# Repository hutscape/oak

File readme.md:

# Oak

> 🌳 Outdoor LoRa-GPS tracker with E-Ink display  🔑

Visit [hutscape.com/oak](https://hutscape.com/oak) for more details.

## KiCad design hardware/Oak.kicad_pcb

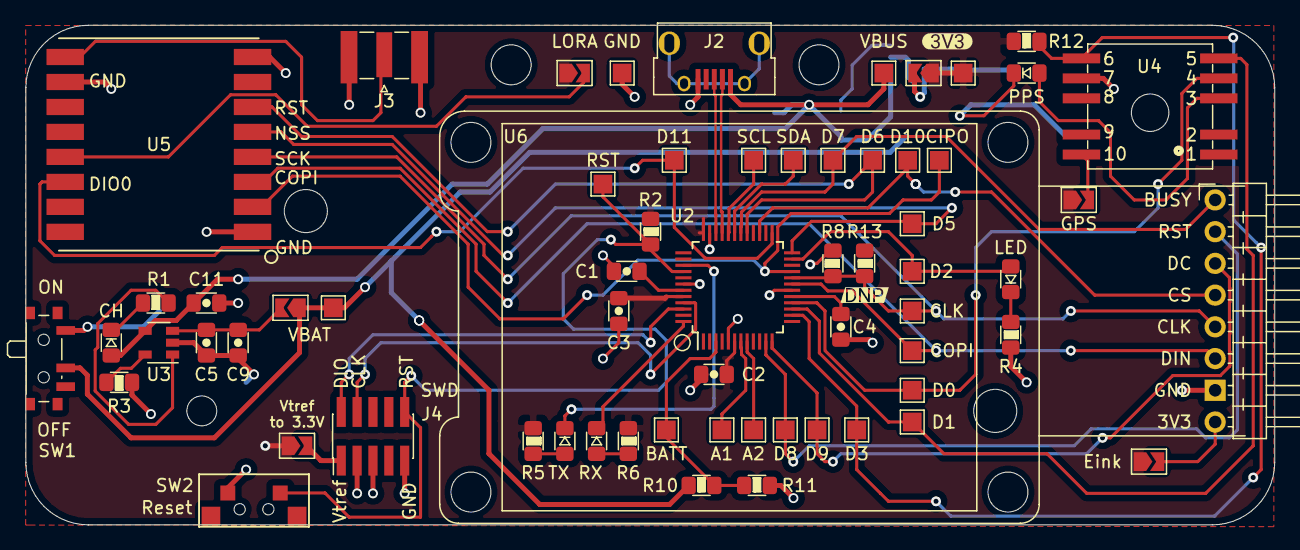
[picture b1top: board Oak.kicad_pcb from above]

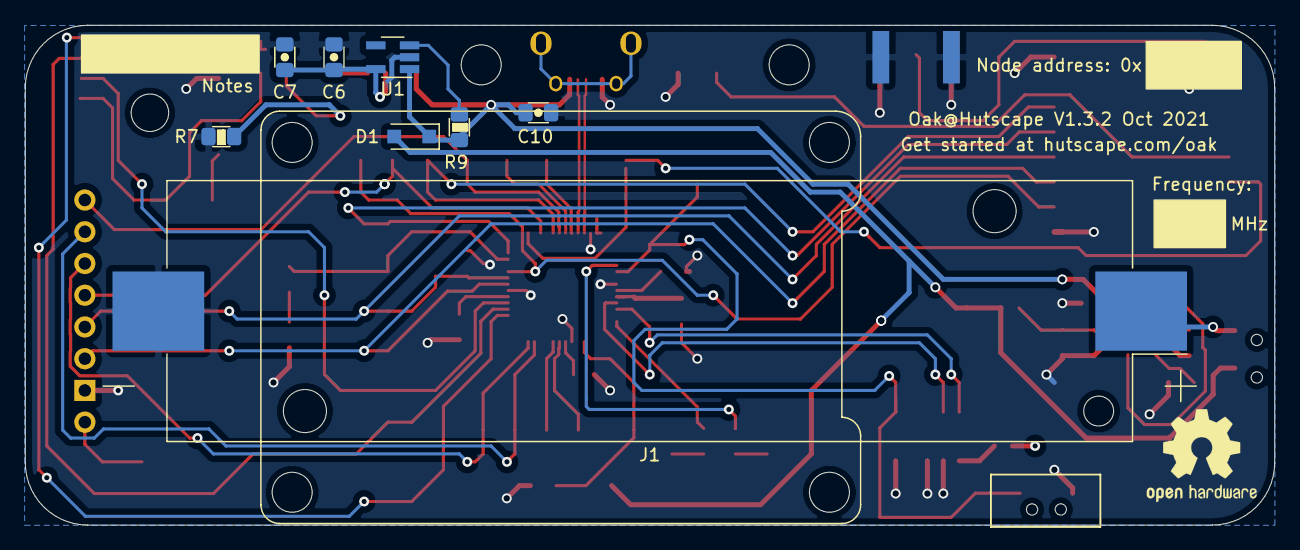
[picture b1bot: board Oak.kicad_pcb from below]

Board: 2 copper layers, 100.0 x 40.0 mm, 73 parts (8 on the bottom side), 48 nets.

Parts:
C1, C7, C9: 1uF; C_0805_2012Metric_Pad1.15x1.40mm_HandSolder
C2, C3, C4: 100nF; C_0805_2012Metric_Pad1.15x1.40mm_HandSolder
C5, C6, C10, C11: 10uF; C_0805_2012Metric_Pad1.15x1.40mm_HandSolder
D1: D_Schottky; D_SOD-123F
D2: ORANGE; LED_0805_2012Metric_Pad1.15x1.40mm_HandSolder
D3: RED; LED_0805_2012Metric_Pad1.15x1.40mm_HandSolder
D4, D5, D6: YELLOW; LED_0805_2012Metric_Pad1.15x1.40mm_HandSolder
J1: 18650 Battery holder; BatteryHolder_Keystone_1042_1x18650
J2: USB_B_Micro; USB_Micro-B_Horizontal-U254-051T-4BH23-S2B
J3: Conn_Coaxial; SMA_Samtec_SMA-J-P-X-ST-EM1_EdgeMount
J4: Conn_ARM_JTAG_SWD_10; PinHeader_2x05_P1.27mm_Vertical_SMD
JP1, JP2, JP3, JP4, JP5, JP6: SolderJumper_2_Open; SolderJumper-2_P1.3mm_Open_TrianglePad1.0x1.5mm
R1, R4, R5, R6, R7, R8: 1k; R_0805_2012Metric_Pad1.15x1.40mm_HandSolder
R2, R3, R12: 10k; R_0805_2012Metric_Pad1.15x1.40mm_HandSolder
R9, R10, R11: 100k; R_0805_2012Metric_Pad1.15x1.40mm_HandSolder
R13: DNP; R_0805_2012Metric_Pad1.15x1.40mm_HandSolder
SW1: SW_SPDT; SW_SPDT_PCM12
SW2: SW_Push; Tactile_pushbutton
TP1, TP2, TP3, TP4, TP5, TP6, TP7, TP8, TP9, TP10, TP11, TP12, TP13, TP14, TP15, TP16, TP17, TP18, TP19, TP20, TP21, TP22, TP23, TP24: TestPoint_Probe; TestPoint_Pad_1.5x1.5mm
U1: AP2112; SOT-23-5_HandSoldering
U2: ATSAMD21; TQFP-48_7x7mm_P0.5mm
U3: MCP7383; SOT-23-5
U4: PA1010D; CDTop_MT3333_PA1010D
U5: RFM95; HopeRF_RFM9X-SMD
U6: Waveshare_1in54_epaper; Waveshare_1.54_E-Ink
e: G***; label
svg2mod: G***; label

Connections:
+3V3: C2.1, C3.1, C4.1, JP1.1, JP3.1, JP4.1, JP5.1, JP6.1, R2.1, R5.1, R6.1, R12.1, R13.1, TP4.1, U2.6, U2.17, U2.36, U2.44
/A1: TP7.1, U2.7
/A2: TP6.1, U2.8
/BATT: R10.2, R11.1, TP8.1, U2.3
/CIPO: TP21.1, U2.21, U5.2
/CLK: R8.1, R13.2, TP16.1, U2.20, U5.4, U6.5
/COPI: TP5.1, U2.19, U5.3, U6.6
/EINK_BUSY: TP19.1, U2.30, U6.1
/EINK_CS: TP22.1, U2.27, U6.4
/EINK_DC: TP10.1, U2.12, U6.3
/EINK_RST: TP9.1, U2.11, U6.2
/GPS_RST: R12.2, TP11.1, U2.14, U4.6
/GPS_RX: TP12.1, U2.15, U4.5
/GPS_TX: TP13.1, U2.16, U4.4
/LED: D6.2, TP14.1, U2.23
/LORA_CS: TP15.1, U2.24, U5.5
/LORA_DATA: TP24.1, U2.25, U5.14
/LORA_RST: TP20.1, U2.29, U5.6
/RST: J4.10, R2.2, SW2.1, TP23.1, U2.40
/RX_LED: D5.1, U2.48
/SCL: TP18.1, U2.32
/SDA: TP17.1, U2.31
/SWCLK: J4.4, U2.45
/SWDIO: J4.2, U2.46
/TX_LED: D4.1, U2.39
/USB_D+: J2.3, U2.34
/USB_D-: J2.2, U2.33
/VBAT: D1.2, JP2.1, R10.1, SW1.2, TP1.1
/VBUS: C10.1, C11.2, D1.1, D2.2, J2.1, R9.2, TP2.1, U1.1, U3.4
GND: C1.1, C2.2, C3.2, C4.2, C5.1, C6.2, C7.2, C9.1, C10.2, C11.1, J1.2, J2.5, J3.2, J4.3, J4.5, J4.9, R3.1, R4.2, R7.2, R8.2, R11.2, SW2.2, TP3.1, U1.2, U2.5, U2.18, U2.35, U2.42, U3.2, U4.7, U5.1, U5.8, U5.10, U6.7
unnamed: C1.2, U2.43
unnamed: C5.2, C9.2, JP2.2, U3.3
unnamed: C6.1, C7.1, JP1.2, U1.5
unnamed: D2.1, R1.1
unnamed: D3.1, R7.1
unnamed: D3.2, U4.3
unnamed: D4.2, R5.2
unnamed: D5.2, R6.2
unnamed: D6.1, R4.1
unnamed: J1.1, SW1.1
unnamed: J3.1, U5.9
unnamed: J4.1, JP6.2
unnamed: JP3.2, U4.10
unnamed: JP4.2, U5.13
unnamed: JP5.2, U6.8
unnamed: R1.2, U3.1
unnamed: R3.2, U3.5
unnamed: R9.1, U1.3

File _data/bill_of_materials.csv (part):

"Designator","Value","Qty","Package","Category","Stock","Manufacturer","MPN","Datasheet","Vendor","Link","Unit","Total","MOQ","Description","DNP"
"C4, C3, C2, ","100nF","3","0805","Electronics","boxA-53","Murata","GCM21BR72A104KA37L","http://www.farnell.com/datasheets/2048170.pdf","Element14","https://sg.element14.com/murata/gcm21br72a104ka37l/cap-0-1-f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","0.207","0.62","5","C_Small: Unpolarized capacitor, small symbol",""
"C5, C6, C10, C11, ","10uF","4","0805","Electronics","boxA-30","Taiyo Yuden","LMK212ABJ106KGHT","http://www.farnell.com/datasheets/2842314.pdf","Element14","https://sg.element14.com/taiyo-yuden/lmk212abj106kght/capaci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","0.252","1.01","1","C_Small: Unpolarized capacitor, small symbol",""
"C7, C9, C1, ","1uF","3","0805","Electronics","boxB-186","Kemet","C0805C105K3RACTU","https://api.kemet.com/component-edge/download/specsheet/C080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","Element14","https://sg.element14.com/kemet/c0805c105k3ractu/cap-1-f-25v-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","0.156 ","0.47","10","C_Small: Unpolarized capacitor, small symbol",""
"D1, ","D_Schottky","1","SOD-123F","Electronics","boxA-52","Nexperia","PMEG3020EH,115","http://www.farnell.com/datasheets/676305.pdf","Element14","https://sg.element14.com/nexperia/pmeg3020eh-115/diode-schot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,115","0.438 ","0.44","5","D_Schottky: Schottky diode",""
"D2, ","ORANGE LED","1","0805","Electronics","","ROHM","SML-211DTT86","http://www.farnell.com/datasheets/2292362.pdf","Element14","https://sg.element14.com/rohm/sml-h12d8tt86/led-orange-63mcd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","0.562","0.562","1","LED: Light emitting diode",""
"D3, ","RED LED","1","0805","Electronics","boxB-187","KINGBRIGHT","KP-2012SURCK","http://www.farnell.com/datasheets/2046343.pdf","Element14","https://sg.element14.com/kingbright/kp-2012surck/led-1-25mm-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","0.474","4.74","5","LED: Light emitting diode",""
"D4, D5, ","YELLOW LED","2","0805","Electronics","boxA-54","Everlight","17-215UYC/S530-A3/TR8","https://datasheet.lcsc.com/szlcsc/1810051702_Everlight-Elec-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","LCSC","https://lcsc.com/product-detail/Light-Emitting-Diodes-LED_08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","0.0624","0.12","10","LED: Light emitting diode",""
"J1, ","18650 polarised Battery holder for button-top batteries","1","SMD","Connector","boxD-power-013","Keystone","1042P","http://www.farnell.com/datasheets/2067690.pdf","Element14","https://sg.element14.com/keystone/1042p/battery-holder-18650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","4.04","4.04","1","Conn_01x02_Female: Generic connector, single row, 01x02, script generated (kicad-library-utils/schlib/autogen/connector/)",""
"J2, ","USB_B_Micro","1","SMD","Connector","boxA-60 ","XKB Connectivity","U254-051T-4BH23-S2B","https://datasheet.lcsc.com/szlcsc/2002271812_XKB-Connectivit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","LCSC","https://lcsc.com/product-detail/USB-Connectors_XKB-Connectiv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","0.0786","0.08","10","USB_B_Micro: USB Micro Type B connector",""
"J3, ","Conn_Coaxial","1","PCB Mount","Connector","boxB-185","Multicomp","MP-19-70-4-TGG","http://www.farnell.com/datasheets/1662283.pdf","Element14","https://sg.element14.com/multicomp/19-70-4-tgg/rf-coaxial-sm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","5.16","5.16","1","Conn_Coaxial: coaxial connector (BNC, SMA, SMB, SMC, Cinch/RCA, ...)",""
"J4, ","Conn_ARM_JTAG_SWD_10","1","SMD","Connector","boxC-boards-017","AliExpress Stlxy ","2x5PIN 1.27mm connector","https://www.aliexpress.com/item/4000979986011.html","AliExpress","https://www.aliexpress.com/item/4000979986011.html","0.126","0.126","10","10PCS SMD SMT 2*5 PIN double row male PIN HEADER 1.27MM PITCH Strip Connector",""
"JP1, JP2, JP3, JP4, JP5, ","SolderJumper_2_Open","5","","Connector","","","","","","","","0","","SolderJumper_2_Open: Solder Jumper, 2-pole, open","JP1, JP2, JP3, JP4, JP5"
"R3, R12, R2, ","10k","3","0805","Electronics","boxA-31","Multicomp","MCWF08P1002FTL","http://www.farnell.com/datasheets/2864032.pdf","Element14","https://sg.element14.com/multicomp/mcwf08p1002ftl/res-10k-1-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","0.01","0.03","10","R_Small: Resistor, small symbol",""
"R5, R6, R8, R7, R1, ","1k","5","0805","Electronics","boxA-18","Multicomp","MCWR08X1001FTL","http://www.farnell.com/datasheets/2563624.pdf","Element14","https://sg.element14.com/multicomp/mcwr08x1001ftl/res-1k-1-0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","0.012","0.06","10","R_Small: Resistor, small symbol",""
"R9, R10, R11, ","100k","3","0805","Electronics","boxA-56","Ralec","RTT051003BTP","https://datasheet.lcsc.com/szlcsc/1810301245_RALEC-RTT051003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","LCSC","https://lcsc.com/product-detail/Chip-Resistor-Surface-Mount_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","0.0472","0.14","20","R_Small: Resistor, small symbol",""
"R13, ","DNP","1","0805","Electronics","boxA-18","Multicomp","MCWR08X1001FTL","http://www.farnell.com/datasheets/2563624.pdf","Element14","https://sg.element14.com/multicomp/mcwr08x1001ftl/res-1k-1-0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","0.012","0.06","10","R_Small: Resistor, small symbol","R13"
"SW1, ","SW_SPDT","1","SMD","Switch","boxA-40","Nidec","CUS-12TB","http://www.farnell.com/datasheets/2604293.pdf","Element14","https://sg.element14.com/nidec-copal/cus-12tb/slide-switch-s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","1.04 ","1.04","5","SW_SPDT: Switch, single pole double throw",""
"SW2, ","SW_Push","1","SMD","Switch","boxA-14","RTLECS","RTLECS Tactile side-actuated switch","https://www.aliexpress.com/item/32645332799.html","AliExpress","https://www.aliexpress.com/item/32645332799.html","0.19","0.19","10","SW_Push: Push button switch, generic, two pins",""
"TP13, TP9, TP12, TP14, TP11, TP15, TP20, TP19, TP22, TP23, TP5, TP21, TP16, TP1, TP2, TP10, TP17, TP18, TP8, TP6, TP7, TP4, TP3, TP24, ","TestPoint_Probe","24","SMD","Electronics","","","","","","","","0","","TestPoint_Probe: test point (alternative probe-style design)","TP13, TP9, TP12, TP14, TP11, TP15, TP20, TP19, TP22, TP23, TP5, TP21, TP16, TP1, TP2, TP10, TP17, TP18, TP8, TP6, TP7, TP4, TP3, TP24, "
"U1, ","AP2112","1","SOT23-5","Electronics","boxA-6","Diodes","AP2112K-3.3TRG1","https://www.diodes.com/assets/Datasheets/AP2112.pdf","Element14","https://sg.element14.com/diodes-inc/ap2112k-3-3trg1/ldo-fixe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","0.483","0.48","5","AP2112K-3.3: 600mA low dropout linear regulator, with enable pin, 3.8V-6V input voltage range, 3.3V fixed positive output, SOT-23-5",""
"U2, ","ATSAMD21","1","TQFP-48","Electronics","boxA-59 ","Atmel","ATSAMD21G18A-AU","http://ww1.microchip.com/downloads/en/DeviceDoc/SAM_D21_DA1_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","Element14","https://sg.element14.com/microchip/atsamd21g18a-au/mcu-32bit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","5.46","5.46","1","ATSAMD21G18A-AUT: SAM D21 Microchip SMART ARM-based Flash MCU, 48Mhz, 256K Flash, 32K SRAM, TQFP-48",""
"U3, ","MCP7383","1","SOT-23-5","Electronics","boxB-158","Microchip","MCP73831T-2ACI/OT","http://ww1.microchip.com/downloads/en/DeviceDoc/20001984g.pdf","Element14","https://sg.element14.com/microchip/mcp73831t-2aci-ot/li-ion-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","0.837","0.84","1","MCP73831-2-OT: Single cell, Li-Ion/Li-Po charge management controller, 4.20V, Tri-State Status Output, in SOT23-5 package",""
"U4, ","PA1010D","1","SMD","Electronics","boxA-51","CDTop","PA1010D","https://drive.google.com/file/d/1O-9RGAwgs2fgtnzJRBa9eB1fAqJ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","CDTop","https://www.cdtop-tech.com/products/pa1010d","12.00","12.0","1","PA1010D: ",""
"U5, ","RFM95","1","SMD","Electronics","boxB-188","HopeRF","RFM95W-915S2","https://www.hoperf.com/data/upload/portal/20181127/5bfcbea20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","Element14","https://sg.element14.com/hoperf/rfm95w-915s2/rf-transceiver-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","24.55","24.55","1","RFM95W-915S2: Low power long range transceiver module, SPI and parallel interface, 915 MHz, spreading factor 6 to12, bandwith 7.8 to 500kHz, -111 to -148 dBm, SMD-16, DIP-16",""
"U6, ","1x8 2.54mm Right-angled pin header","1","Connector","Electronics","boxA-46","AMPHENOL ICC","	68016-208HLF","http://www.farnell.com/datasheets/2357893.pdf","Element14","https://sg.element14.com/amphenol-icc/68016-208hlf/conn-head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","0.747","0.747","1","CONN, HEADER, R/A, 8POS, 1ROW, 2.54MM",""
"U7, ","Waveshare_1in54_epaper","1","Module","Electronics","boxC-boards-025","Waveshare","614961950511","https://www.waveshare.com/1.54inch-e-Paper-Module.htm","Waveshare","https://www.waveshare.com/1.54inch-e-Paper-Module.htm","21.21","21.21","1","Waveshare_1in54_epaper: ",""
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
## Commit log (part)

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2020-10-12 feat: organize intial firmware with GPS and E-ink features
2020-10-13 docs: add a note and references for SPI conflicts in LoRa and E-ink
2020-10-13 update: update jekyll and kramdown
2020-10-13 refactor: gitignore kicad backup file
2020-10-13 fix: e-ink is no longer printing extra char with null character. close #4
2020-10-20 feat: add pin mapping info for Arduino Zero and SAMD21G
2020-10-21 feat: add reset and TX/RX LEDs
2020-10-26 docs: add links to firmware libraries for E-ink and GPS
2020-10-26 refactor: move lora to src folder
2020-11-17 feat: add lipo charging, micro-usb and breakout lora to schematic
2020-11-18 refactor: update schematic PDF
2020-11-18 refactor: update new schematic PDF
2020-11-23 refactor: add decoupling caps and fix net labels
2020-11-25 docs: add biggest part dimensions
2020-12-09 docs: add LilyGO TTGO T-Beam as a similar project
2020-12-17 docs: add links for references
2021-01-20 data: add BOM columns for LEDs and associate footprints for all 0805
2021-01-20 feat: explort netlist and create rats nest
2021-01-21 chore: update git submodule scripts
2021-01-21 docs: update XML file
2021-01-25 chore: update kicad xml
2021-03-30 chore(deps): bump kramdown from 2.3.0 to 2.3.1
    Bumps [kramdown](https://github.com/gettalong/kramdown) from 2.3.0 to 2.3.1.
    - [Release notes](https://github.com/gettalong/kramdown/releases)
    - [Changelog](https://github.com/gettalong/kramdown/blob/master/doc/news.page)
    - [Commits](https://github.com/gettalong/kramdown/commits)
2021-04-06 refactor: change from LiPo to 18650 battery
2021-04-06 feat: add XH2.54 JST 2.54mm Pitch 8pin connector for e-ink
2021-04-06 fix: fix spelling, submodule https url and extra BOM
2021-04-07 feat: remove all traces to focus on placement first
2021-04-29 feat: new netlist, new PCB layout
2021-04-29 feat: import new ratsnest
2021-04-29 feat: move logical block lipo charging components into a seperate block
2021-05-04 feat: move logical block gps components into a seperate block
2021-05-05 feat: move logical block lora components into a seperate block
2021-05-05 feat: move logical block mcu components into a seperate block
2021-05-06 chore: update dependancies
2021-05-09 feat: place all components on PCB with silkscreen labels
2021-05-10 feat: fix all clearance issues with local clearance settings
2021-05-14 feat: add more routes (22 remaining unconnected)
2021-05-15 feat: add more routes (11 remaining unconnected)
2021-05-15 feat: add more routes (0 remaining unconnected)
2021-05-16 refactor: enable courtyard check for M3 mounting holes
2021-05-16 chore: update all images and docs
2021-05-18 refactor: connect both TX and RX of GPS module (4 unconnected)
2021-05-19 feat: complete route for LORA data and connect both TX and RX to GPS module
2021-05-21 feat: add bill of material info on extra items and stats. #19
2021-05-21 feat: generate iBOM
2021-05-23 feat: add 2 M3 mechanical NPTH holes for hanging/mounting the PCB. #19
2021-05-26 docs: change power to 18650
2021-05-26 docs: change RED LED in Bill of Materials
2021-05-29 chore: update files
2021-05-30 docs: add U6 pin header and U7 E-ink display for BOM
2021-05-31 fix: change SMA connector to 0.25 inch
2021-05-31 chore: regenerate iBom
2021-06-04 chore: add right-angled pin header delivery
2021-06-09 fix: fix DNP R13 in BOM and iBOM
2021-06-19 docs: re-generate BOM using updated scripts
2021-06-23 docs: add schedule dates
2021-06-25 chore: upgrade iBOM
2021-06-25 feat: add kitspace yaml. closes #21
2021-06-26 refactor: use Qty instead of Q for BOM display
2021-06-27 chore: cleanup dependancies
2021-06-28 docs: add lessons learnt page
2021-06-29 docs: add steps for bringing up the board
2021-06-29 docs: add a note on putting ground as a test point with clip
2021-06-30 docs: change 10k resistor from Mouser to Element14 Farnell
2021-07-02 refactor: add an option to not connect Vtref for SWD for J-Link Edu mini
2021-07-13 chore: update ibom
2021-07-22 refactor: align net label
2021-07-23 fix: amend a 90deg track
2021-08-10 fix: remove fixed top navbar
2021-08-12 fix: amend relative url for examples
2021-08-23 refactor: combine lessons, references and schedule pages into others
2021-08-26 fix: remove unused pages.yml
2021-08-26 feat: add examples
2021-08-26 refator: seperate layouts and includes as submodules
2021-08-29 feat: add dependancies and videos to examples. close #27
2021-09-09 docs: explain the requirement for button-top 18560 batteries
2021-09-10 feat: add blinky LED hello world photos
2021-09-10 feat: add serial prints for hello world example
2021-09-22 feat: add blinky LED for measuring batt
2021-09-23 refactor: improve visual blinky indication for LoRa transmission example
2021-10-05 fix: change LoRa CIPO pin from PA19 (D12) to PA12
2021-10-05 fix: use PORT variable to upload firmware
2021-10-05 feat: add example of lora duplex
2021-10-05 fix: add back download buttons
2021-10-06 docs: add e-ink example code
2021-10-07 docs: add notes on V2 iteration
2021-10-07 docs: add example code to test GPS
2021-10-08 refactor: reorder tutorials on navbar
2021-10-19 docs: annotate image for uploading bootloader
2021-10-20 docs: add more prerequisit URLs and todo prorotype image
2021-10-23 chore: update gems and submodule
2021-10-23 docs: add more details to custom board
2021-10-25 refactor: display more features on eink
2021-11-11 docs: add 4 view images
2021-11-11 docs: add GPS prototype setup photos
2021-11-11 docs: add eink prototype image
2021-11-11 docs: update getting started instructions
2021-11-22 feat: add example demo code with LoRa P2P communication
2021-11-30 refactor: add newlines
2021-12-01 feat: add demo code to get a GPS fix and display on E-Ink
2021-12-02 feat: serial print more GPS info
2021-12-03 refactor: remove all serial prints to prepare for debug toggle print
2021-12-03 refactor: do not display milliseconds time on E-Ink
2021-12-03 fix: print the correct timezone adjusted time
2021-12-03 refactor: add internal folders for Intellisense
2021-12-04 refactor: simplify Makefile to use hutscape:samd:oak as FQBN
2021-12-08 docs: update getting started instructions Step 3
2021-12-10 docs: better Steps section for examples
2021-12-13 refactor: simplify all Makefiles to use hutscape:samd:oak as FQBN
2021-12-14 docs: add tutorial on LoRa GPS duplex example B
2021-12-15 refactor: initialise GPSRST pin to HIGH
2021-12-16 fix: use the correct SerialUSB for printing
2021-12-16 feat: add e-paper versions to examples
2021-12-17 docs: add new example for reading and writing to the flash
2021-12-18 docs: add new example for reading and writing struct to the flash
2021-12-18 refactor: increase accuracy of GPS location to 8 decimals places
2021-12-21 refactor: add example for converting DMS to Decimal degrees
2021-12-23 feat: add 3 levels of printing debug messages
2021-12-24 feat: display lat-long and gps time on E-Ink screen
2021-12-26 feat: add compiler flags to change local and destination address
2021-12-27 fix: use symlinks to interchange eink library versions
2021-12-28 refactor: insert more debug prints on the node addresses
2021-12-28 refactor: abstract into initEink and displayOnEink functions
2021-12-28 feat: add Haversine function
2021-12-31 refactor: display initial messages on the E-Ink without a fix or peer
2021-12-31 refactor: create a valid GPS fix upon receiving the peer node info
2022-01-05 feat: fast blink the LED when waiting for GPS fix
2022-01-08 docs: add power section
2022-01-11 docs: add lessons learned points
2022-01-13 fix: process peer lat-long after receiving in LoRa immediately
2022-01-13 refactor: amend fast blink function to sync the number of blinks with the argument
2022-01-16 refactor: rename bool function to check if it is ok to calculate the Haversine distance
2022-01-18 refactor: change long data type to uint32_t
2022-02-07 refactor: add debug message when calculating the Haversine distance
2022-02-16 fix: remove unused environment variable for EINK_V2
2022-03-08 docs: add notes on charging and discharging batt
2022-03-09 feat: add favicons to project head
2022-03-09 chore: update anchor.js from 4.2.0 to 4.3.1
2022-03-14 chore: upgrade to KiCad 6
2022-03-16 chore: update for Monterey
2022-04-13 docs: remove url in similar project section
2022-04-13 "feat: add monthly progress in scehdule"
2022-04-13 refactor: remove unused version
2022-04-20 "refactor: sync status tags and update footer"
2022-04-20 "refactor: put the download links first on the start page"
2022-04-21 refactor: remove repeated status completed tag
2022-04-21 feat: add new gitmodule and intall them upon creating new project
2022-04-21 "refactor: seperate BOM page into more partials"
2022-04-22 refactor: seperate example page content into partials
2022-04-22 feat: add initial FreeCAD files for enclosure
2022-05-13 "feat: add VSCode text editor and FreeCAD files to gitignore"
2022-05-13 feat: add antenna connector and E-Ink screen slots
2022-05-13 feat: extrude PPS and CH LED texts
2022-05-14 feat: cut slots and electronics contents
2022-05-15 feat: create one screw lug
2022-05-16 refactor: add measurements
2022-05-17 feat: export top and bottom part of the enclosure in STL
2022-05-18 feat: add grid origin
2022-05-18 chore: export both top and bottom parts of the case
2022-05-19 feat: add 3D model of stub antenna in FreeCAD KiCAD integration
2022-05-19 feat: add Waveshare Eink 1.54in screen as a 3D model
2022-05-19 feat: create /case to link CAD and STL files with photos
2022-05-19 "refactor: improve FreeCAD file name and link"
2022-06-03 fix: change screw diameter to 2.8mm for self-tapping screws
2022-06-06 chore: export bottom STL for the case
2022-07-21 refactor: rename hardware layout to pcb
2022-07-21 refactor: rename examples to code
2022-07-22 fix: change link to images for code
2022-07-22 "fix: change GitHub URL for HTML code examples"
2022-07-22 chore: move images from hardware to pcb directory
2022-07-25 feat: add 3d printed case photos
2022-07-25 refactor: move code list to includes
2023-10-28 chore: update gitsubmodules
2024-02-26 feat: update submodules for unique SMT, DNP and TH BOM parts
2024-02-29 docs: add update and uncommit in Makefile
2024-02-29 chore: update submodules to seperate /case page into sections
2024-03-04 fix: add check for an extra empty empty image slot only if there are odd images
2024-03-15 chore: update submodules to display software bill of materials
2024-03-22 fix: change YAML spelling error
2024-03-29 chore: update submodules to remove unused Others page
2024-03-29 chore: update submodule to add a link to FreeCAD file download
2024-04-01 chore: update submodules to hyperlink images
2024-04-11 feat: add a new power page
2024-04-12 chore: update submodules to upgrade to latest JS and CSS libraries
2024-05-01 chore: update submodules to sync BOM stats with the manufacturer
2024-05-04 fix: update broken link to demo code
2024-05-06 chore: update submodules to remove unused link to software downloads
2024-05-16 chore(deps): bump rexml from 3.2.6 to 3.2.8
    Bumps [rexml](https://github.com/ruby/rexml) from 3.2.6 to 3.2.8.
    - [Release notes](https://github.com/ruby/rexml/releases)
    - [Changelog](https://github.com/ruby/rexml/blob/master/NEWS.md)
    - [Commits](https://github.com/ruby/rexml/compare/v3.2.6...v3.2.8)
    ---
    updated-dependencies:
2024-08-22 chore(deps): bump rexml from 3.3.0 to 3.3.6
    Bumps [rexml](https://github.com/ruby/rexml) from 3.3.0 to 3.3.6.
    - [Release notes](https://github.com/ruby/rexml/releases)
    - [Changelog](https://github.com/ruby/rexml/blob/master/NEWS.md)
    - [Commits](https://github.com/ruby/rexml/compare/v3.3.0...v3.3.6)
    ---
    updated-dependencies:
2024-10-11 chore: update submodule to fix checkbox mobile view
2024-11-08 docs: update navbar
2024-11-14 chore: update submodule to conditionally display edit button

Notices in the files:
hardware/Oak.kicad_pcb:
License: CC-BY-SA 4.0 or TAPR
